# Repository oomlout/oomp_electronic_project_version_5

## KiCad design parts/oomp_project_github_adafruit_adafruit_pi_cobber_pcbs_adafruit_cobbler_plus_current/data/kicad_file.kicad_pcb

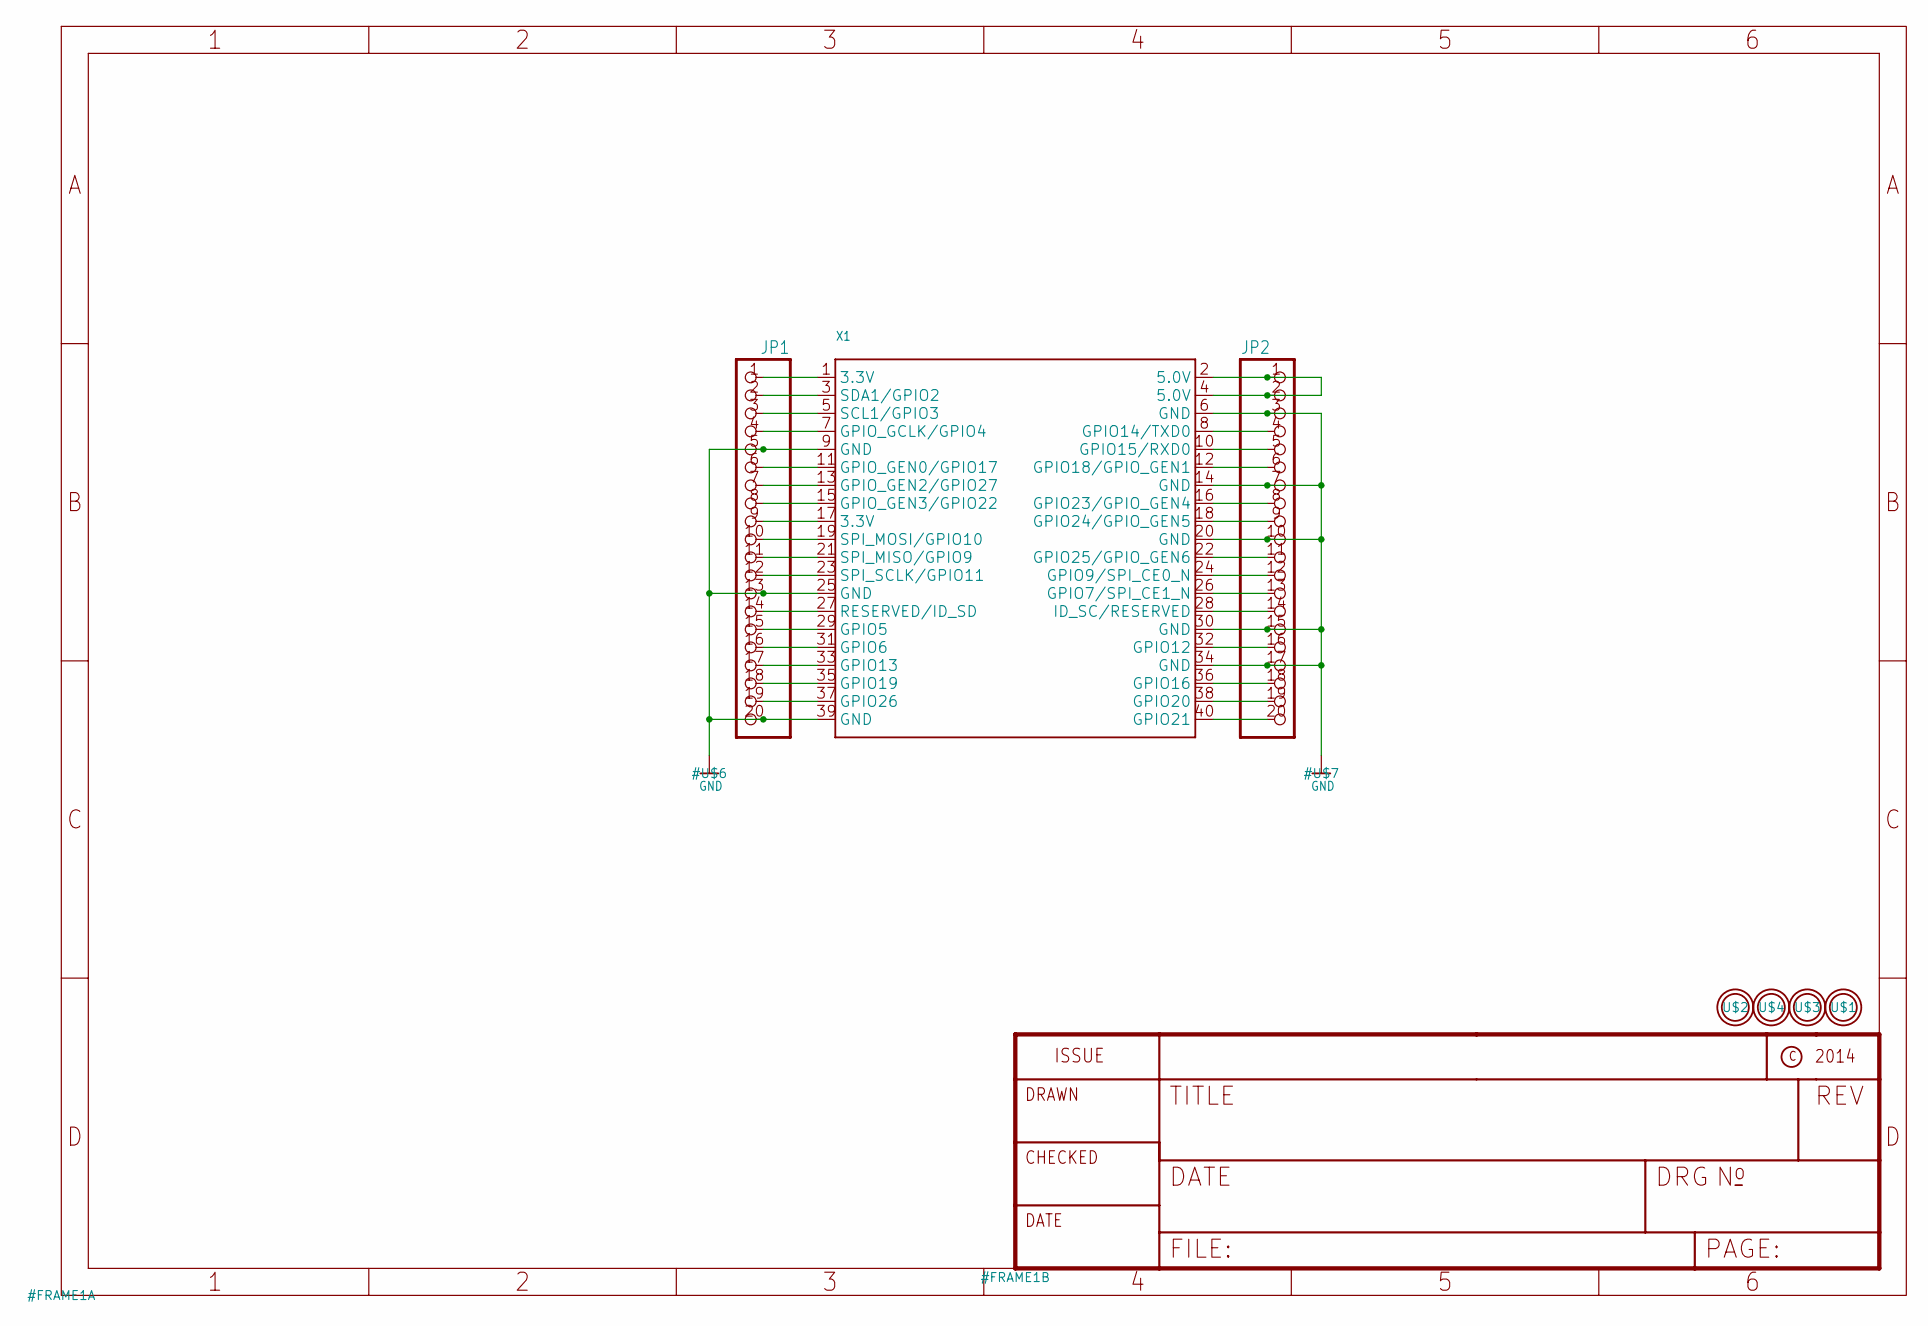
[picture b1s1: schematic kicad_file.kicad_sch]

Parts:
JP1, JP2: HEADER-1X20ROUND; 1X20_ROUND
U$1, U$2, U$3, U$4: MOUNTINGHOLE2.5_THICK; MOUNTINGHOLE_2.5_PLATED_THICK
X1: RASPBERRYPI_B+_IDC

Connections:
GND: JP1.5, JP1.13, JP1.20, JP2.3, JP2.7, JP2.10, JP2.15, JP2.17, X1.6 (GND), X1.9 (GND), X1.14 (GND), X1.20 (GND), X1.25 (GND), X1.30 (GND), X1.34 (GND), X1.39 (GND)
unnamed: JP2.1, JP2.2, X1.2 (5.0V), X1.4 (5.0V)
unnamed: JP2.4, X1.8 (GPIO14/TXD0)
unnamed: JP2.5, X1.10 (GPIO15/RXD0)
unnamed: JP2.6, X1.12 (GPIO18/GPIO_GEN1)
unnamed: JP2.8, X1.16 (GPIO23/GPIO_GEN4)
unnamed: JP2.9, X1.18 (GPIO24/GPIO_GEN5)
unnamed: JP2.11, X1.22 (GPIO25/GPIO_GEN6)
unnamed: JP2.12, X1.24 (GPIO9/SPI_CE0_N)
unnamed: JP2.13, X1.26 (GPIO7/SPI_CE1_N)
unnamed: JP2.14, X1.28 (ID_SC/RESERVED)
unnamed: JP2.16, X1.32 (GPIO12)
unnamed: JP2.18, X1.36 (GPIO16)
unnamed: JP2.19, X1.38 (GPIO20)
unnamed: JP2.20, X1.40 (GPIO21)
unnamed: JP1.1, X1.1 (3.3V)
unnamed: JP1.2, X1.3 (SDA1/GPIO2)
unnamed: JP1.3, X1.5 (SCL1/GPIO3)
unnamed: JP1.4, X1.7 (GPIO_GCLK/GPIO4)
unnamed: JP1.6, X1.11 (GPIO_GEN0/GPIO17)
unnamed: JP1.7, X1.13 (GPIO_GEN2/GPIO27)
unnamed: JP1.8, X1.15 (GPIO_GEN3/GPIO22)
unnamed: JP1.9, X1.17 (3.3V)
unnamed: JP1.10, X1.19 (SPI_MOSI/GPIO10)
unnamed: JP1.11, X1.21 (SPI_MISO/GPIO9)
unnamed: JP1.12, X1.23 (SPI_SCLK/GPIO11)
unnamed: JP1.14, X1.27 (RESERVED/ID_SD)
unnamed: JP1.15, X1.29 (GPIO5)
unnamed: JP1.16, X1.31 (GPIO6)
unnamed: JP1.17, X1.33 (GPIO13)
unnamed: JP1.18, X1.35 (GPIO19)
unnamed: JP1.19, X1.37 (GPIO26)

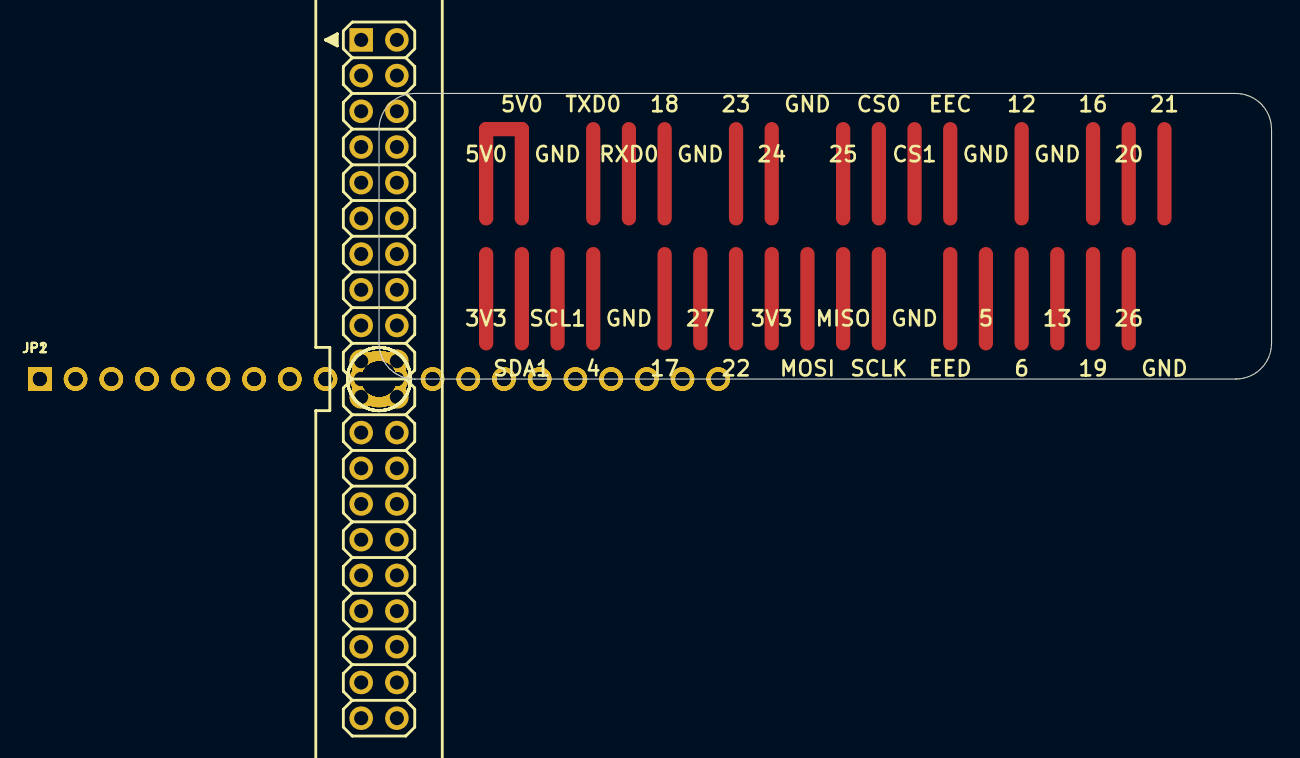
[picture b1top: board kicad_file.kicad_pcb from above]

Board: 2 copper layers, 63.5 x 20.3 mm, 7 parts (0 on the bottom side), 32 nets.

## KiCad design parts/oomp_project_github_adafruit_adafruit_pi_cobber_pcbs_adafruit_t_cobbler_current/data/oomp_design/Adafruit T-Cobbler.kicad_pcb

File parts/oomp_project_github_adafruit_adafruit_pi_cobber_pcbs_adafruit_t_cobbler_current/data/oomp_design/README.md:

# OOMP KiCad design copy

Open `Adafruit T-Cobbler.kicad_pro` (or the `.kicad_pcb` / `.kicad_sch`) in KiCad. Local OOMP libraries are under `libraries/`. Original inputs are preserved in [../original/](../original/).

Only verified unchanged installed KiCad defaults were renamed. Modified, custom, unmatched and unavailable items remain unchanged. Soldering variants are never swapped during conversion. Existing pad coordinates, nets and UUIDs are preserved.

See [conversion_report.yaml](conversion_report.yaml) for every conversion and skip. Copy this directory before editing; regeneration refuses to overwrite edited design files.

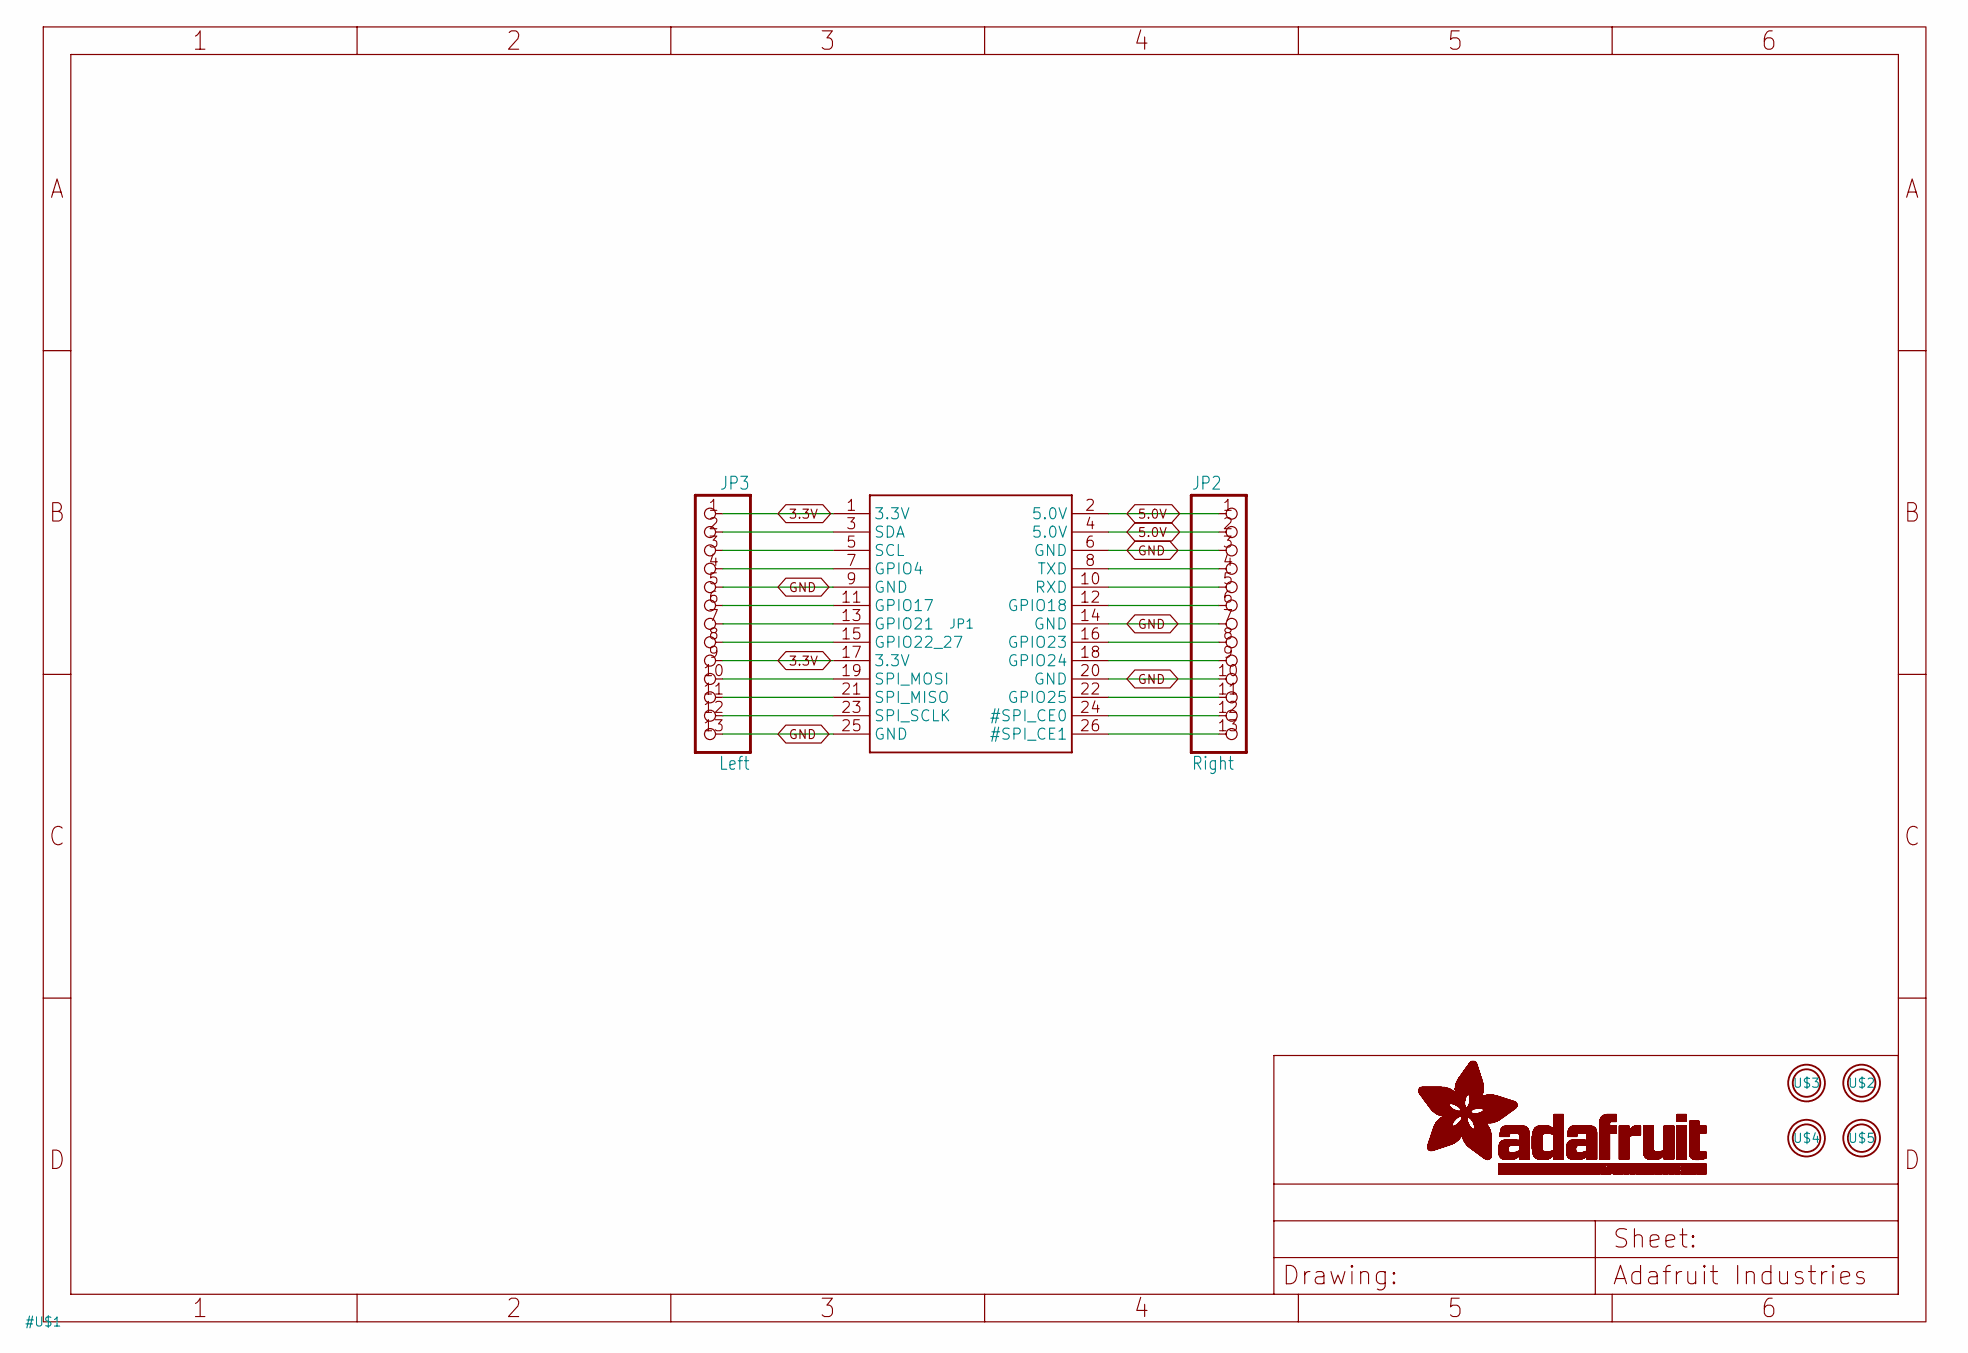
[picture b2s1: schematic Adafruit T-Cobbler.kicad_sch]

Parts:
JP1: PI; RASBERRYPI_IDC
JP2: Right; 1X13_ROUND_70
JP3: Left; 1X13_ROUND_70
U$2, U$3, U$4, U$5: MOUNTINGHOLE2.5; MOUNTINGHOLE_2.5_PLATED

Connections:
3.3V: JP1.1 (3.3V), JP1.17 (3.3V), JP3.1, JP3.9
5.0V: JP1.2 (5.0V), JP1.4 (5.0V), JP2.1, JP2.2
GND: JP1.6 (GND), JP1.9 (GND), JP1.14 (GND), JP1.20 (GND), JP1.25 (GND), JP2.3, JP2.7, JP2.10, JP3.5, JP3.13
unnamed: JP1.3 (SDA), JP3.2
unnamed: JP1.5 (SCL), JP3.3
unnamed: JP1.7 (GPIO4), JP3.4
unnamed: JP1.11 (GPIO17), JP3.6
unnamed: JP1.13 (GPIO21), JP3.7
unnamed: JP1.15 (GPIO22_27), JP3.8
unnamed: JP1.19 (SPI_MOSI), JP3.10
unnamed: JP1.21 (SPI_MISO), JP3.11
unnamed: JP1.23 (SPI_SCLK), JP3.12
unnamed: JP1.8 (TXD), JP2.4
unnamed: JP1.10 (RXD), JP2.5
unnamed: JP1.12 (GPIO18), JP2.6
unnamed: JP1.16 (GPIO23), JP2.8
unnamed: JP1.18 (GPIO24), JP2.9
unnamed: JP1.22 (GPIO25), JP2.11
unnamed: JP1.24 (#SPI_CE0), JP2.12
unnamed: JP1.26 (#SPI_CE1), JP2.13

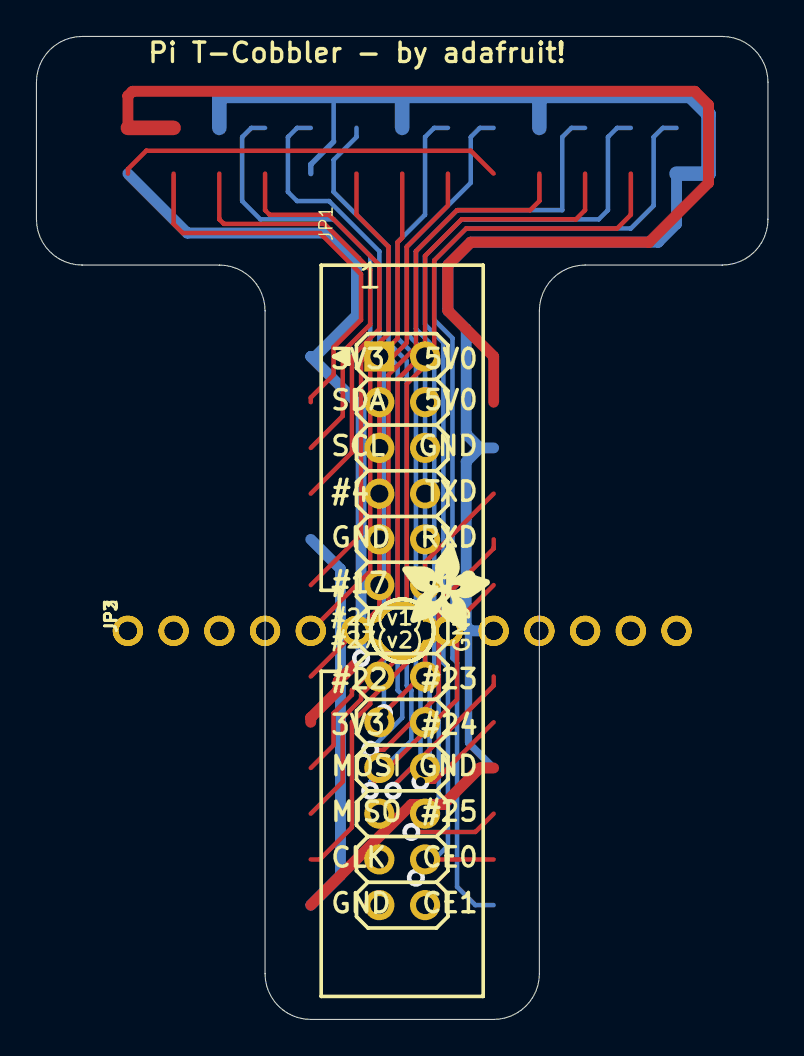
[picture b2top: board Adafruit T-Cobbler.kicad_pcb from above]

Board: 2 copper layers, 40.6 x 54.6 mm, 8 parts (0 on the bottom side), 20 nets.

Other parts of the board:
U$7: ADAFRUIT_5MM

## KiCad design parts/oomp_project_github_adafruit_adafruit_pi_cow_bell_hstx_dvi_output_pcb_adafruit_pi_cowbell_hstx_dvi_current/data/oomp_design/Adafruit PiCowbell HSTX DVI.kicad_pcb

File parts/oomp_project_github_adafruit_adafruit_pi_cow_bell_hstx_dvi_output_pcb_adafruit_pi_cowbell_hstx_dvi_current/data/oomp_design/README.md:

# OOMP KiCad design copy

Open `Adafruit PiCowbell HSTX DVI.kicad_pro` (or the `.kicad_pcb` / `.kicad_sch`) in KiCad. Local OOMP libraries are under `libraries/`. Original inputs are preserved in [../original/](../original/).

Only verified unchanged installed KiCad defaults were renamed. Modified, custom, unmatched and unavailable items remain unchanged. Soldering variants are never swapped during conversion. Existing pad coordinates, nets and UUIDs are preserved.

See [conversion_report.yaml](conversion_report.yaml) for every conversion and skip. Copy this directory before editing; regeneration refuses to overwrite edited design files.

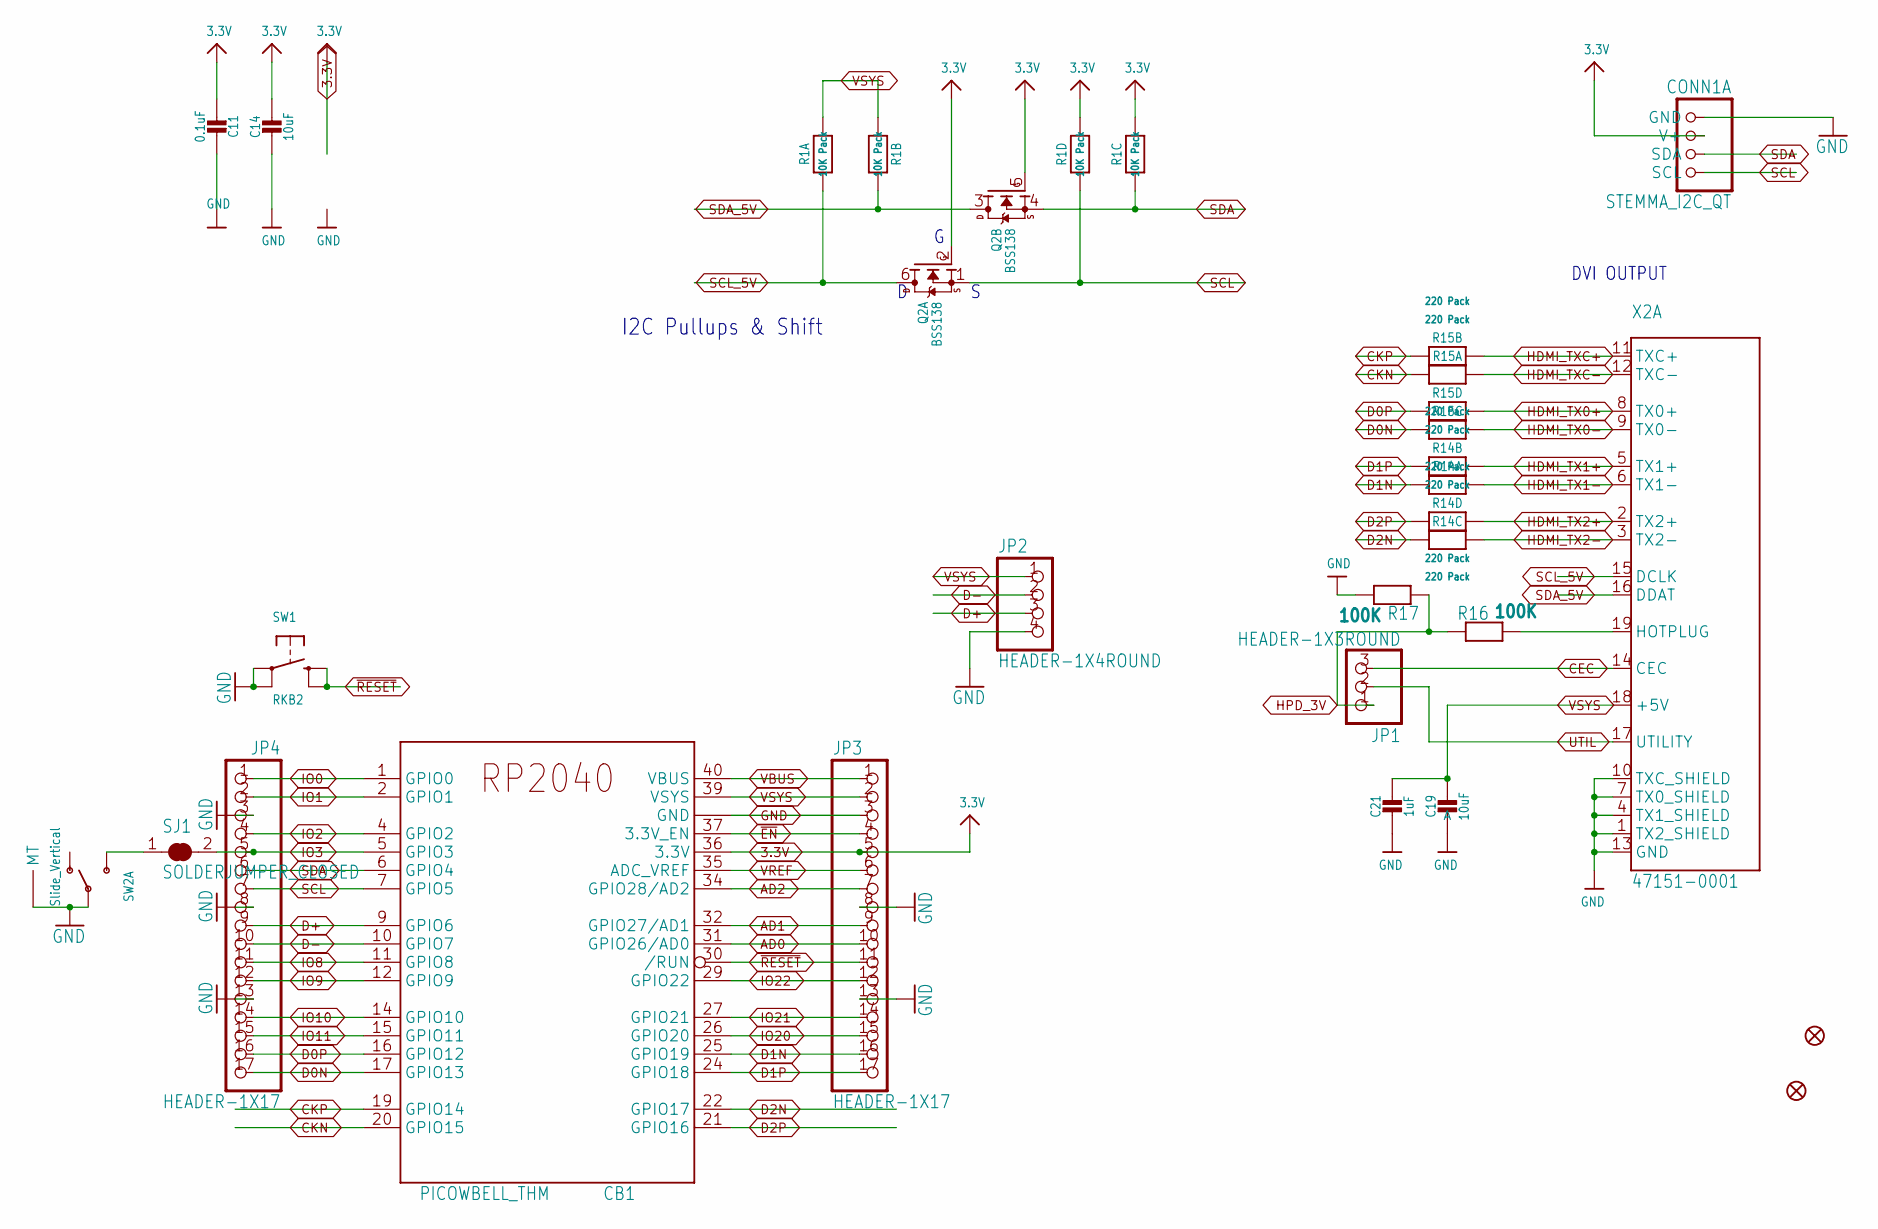
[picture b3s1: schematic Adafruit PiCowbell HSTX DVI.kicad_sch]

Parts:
C11: 0.1uF; 0603-NO
C14, C19: 10uF; 0805-NO
C21: 1uF; 0603-NO
CB1: PICOWBELL_THM
CONN1: STEMMA_I2C_QT; JST_SH4; LCSC C2845363
FID1, FID2: FIDUCIAL_1MM
JP1: HEADER-1X3ROUND; 1X03_ROUND
JP2: HEADER-1X4ROUND; 1X04_ROUND
JP3, JP4: HEADER-1X17; 1X17_ROUND70
Q2: BSS138; SOT363; JLC_ROTATION 270
R1: 10K Pack; RESPACK_4X0603
R14, R15: 220 Pack; RESPACK_4X0603
R16, R17: 100K; 0603-NO
SJ1: SOLDERJUMPER_CLOSED; SOLDERJUMPER_CLOSEDWIRE
SW1: RKB2; BTN_RKB2_4.6X2.8
SW2: Slide_Vertical; SPDT_SMT_SSSS811101
X2: 47151-0001; MINIHDMI_CNCTECH

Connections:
3.3V: C11.2, C14.1, CB1.36 (3.3V), CONN1.2 (V+), JP3.5, Q2.2 (G), Q2.5 (G), R1.5 (2), R1.6 (2)
AD0: CB1.31 (GPIO26/AD0), JP3.10
AD1: CB1.32 (GPIO27/AD1), JP3.9
AD2: CB1.34 (GPIO28/AD2), JP3.7
CEC: JP1.3, X2.14 (CEC)
CKN: CB1.20 (GPIO15), R15.8 (2)
CKP: CB1.19 (GPIO14), R15.7 (2)
D0N: CB1.17 (GPIO13), JP4.17, R15.6 (2)
D0P: CB1.16 (GPIO12), JP4.16, R15.5 (2)
D1N: CB1.25 (GPIO19), JP3.16, R14.8 (2)
D1P: CB1.24 (GPIO18), JP3.17, R14.7 (2)
D2N: CB1.22 (GPIO17), R14.6 (2)
D2P: CB1.21 (GPIO16), R14.5 (2)
D+: CB1.9 (GPIO6), JP2.3, JP4.9
D-: CB1.10 (GPIO7), JP2.2, JP4.10
GND: C11.1, C14.2, C19.2, C21.2, CB1.3 (GND), CB1.8 (GND), CB1.13 (GND), CB1.18 (GND), CB1.23 (GND), CB1.28 (GND), CB1.33 (GND), CB1.38 (GND), CONN1.1 (GND), JP2.4, JP3.3, JP3.8, JP3.13, JP4.3, JP4.8, JP4.13, R17.2, SW1.A, SW1.A' (P1), SW2.B, SW2.SUP1 (MT), SW2.SUP2 (MT), SW2.SUP3 (MT), SW2.SUP4 (MT), X2.1 (TX2_SHIELD), X2.4 (TX1_SHIELD), X2.7 (TX0_SHIELD), X2.10 (TXC_SHIELD), X2.13 (GND), X2.MNT1 (GND), X2.MNT2 (GND), X2.MNT3 (GND), X2.MNT4 (GND)
HDMI_TX0+: R15.4 (1), X2.8 (TX0+)
HDMI_TX0-: R15.3 (1), X2.9 (TX0-)
HDMI_TX1+: R14.2 (1), X2.5 (TX1+)
HDMI_TX1-: R14.1, X2.6 (TX1-)
HDMI_TX2+: R14.4 (1), X2.2 (TX2+)
HDMI_TX2-: R14.3 (1), X2.3 (TX2-)
HDMI_TXC+: R15.2 (1), X2.11 (TXC+)
HDMI_TXC-: R15.1, X2.12 (TXC-)
HPD: R16.2, X2.19 (HOTPLUG)
HPD_3V: JP1.1, R16.1, R17.1
IO0: CB1.1 (GPIO0), JP4.1
IO1: CB1.2 (GPIO1), JP4.2
IO2: CB1.4 (GPIO2), JP4.4
IO3: CB1.5 (GPIO3), JP4.5, SJ1.2
IO8: CB1.11 (GPIO8), JP4.11
IO9: CB1.12 (GPIO9), JP4.12
IO10: CB1.14 (GPIO10), JP4.14
IO11: CB1.15 (GPIO11), JP4.15
IO20: CB1.26 (GPIO20), JP3.15
IO21: CB1.27 (GPIO21), JP3.14
IO22: CB1.29 (GPIO22), JP3.12
unnamed: SJ1.1, SW2.C (S)
SCL: CB1.7 (GPIO5), CONN1.4 (SCL), JP4.7, Q2.1 (S), R1.4 (1)
SCL_5V: Q2.6 (D), R1.8 (2), X2.15 (DCLK)
SDA: CB1.6 (GPIO4), CONN1.3 (SDA), JP4.6, Q2.4 (S), R1.3 (1)
SDA_5V: Q2.3 (D), R1.7 (2), X2.16 (DDAT)
UTIL: JP1.2, X2.17 (UTILITY)
VBUS: CB1.40 (VBUS), JP3.1
VREF: CB1.35 (ADC_VREF), JP3.6
VSYS: C19.1, C21.1, CB1.39 (VSYS), JP2.1, JP3.2, R1.1, R1.2 (1), X2.18 (+5V)
~EN: CB1.37 (3.3V_EN), JP3.4
~RESET: CB1.30 (/RUN), JP3.11, SW1.B (S), SW1.B' (S1)

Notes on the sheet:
DVI OUTPUT
I2C Pullups & Shift

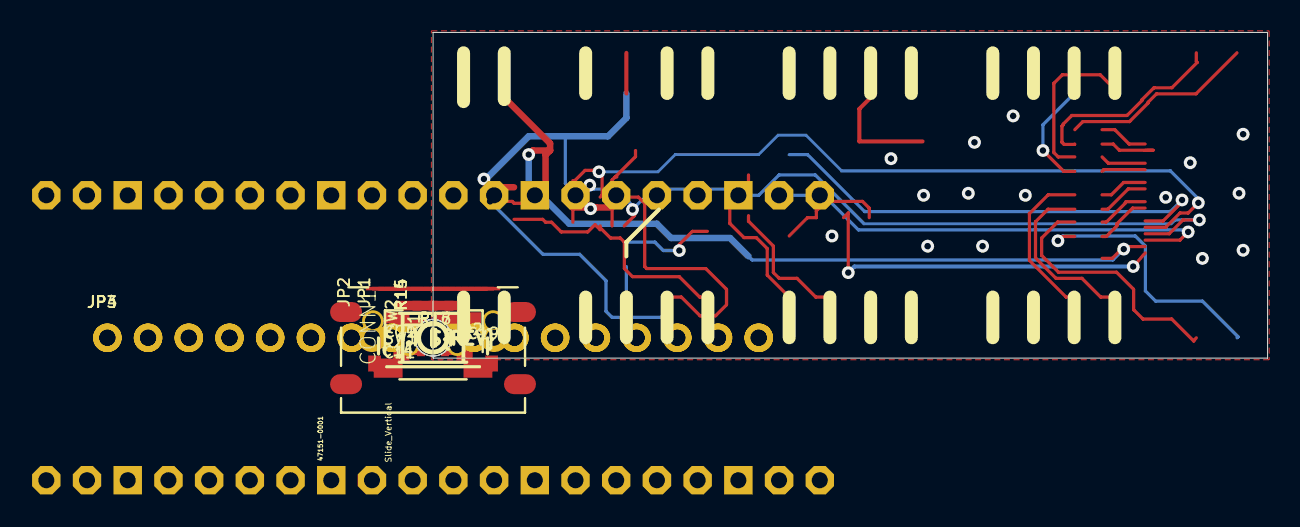
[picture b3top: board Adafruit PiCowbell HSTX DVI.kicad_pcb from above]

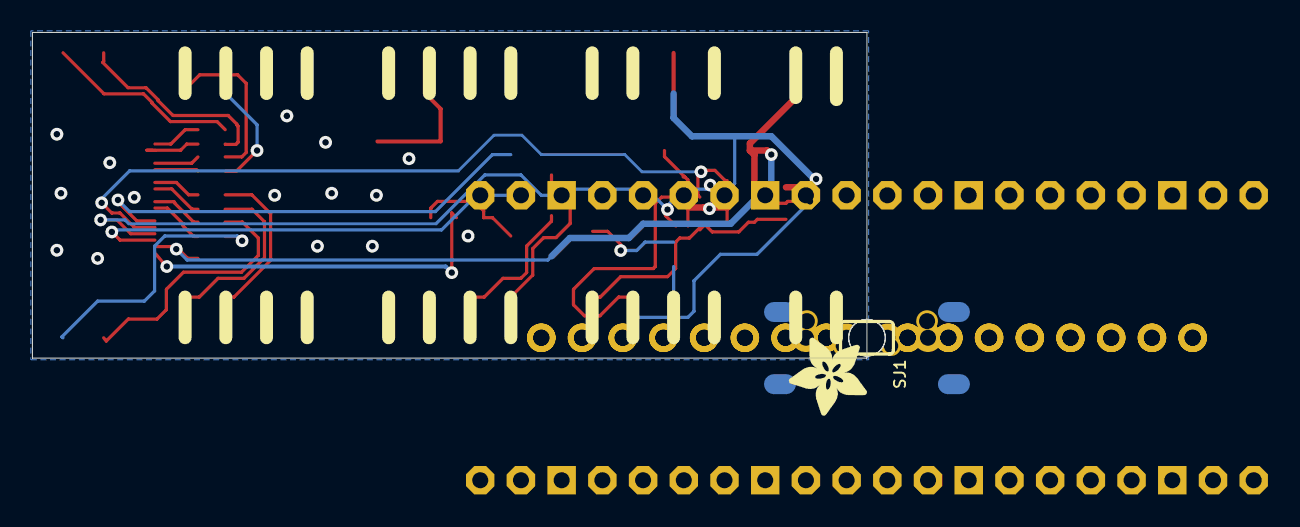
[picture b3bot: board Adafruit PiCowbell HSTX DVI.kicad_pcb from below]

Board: 2 copper layers, 52.1 x 20.3 mm, 110 parts (44 on the bottom side), 48 nets.

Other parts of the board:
PLABEL109: PLABEL109
PLABEL110: PLABEL110
PLABEL111: PLABEL111
PLABEL112: PLABEL112
PLABEL113: PLABEL113
PLABEL114: PLABEL114
PLABEL115: PLABEL115
PLABEL116: PLABEL116
PLABEL117: PLABEL117
PLABEL118: PLABEL118
PLABEL119: PLABEL119
PLABEL120: PLABEL120
PLABEL121: PLABEL121
PLABEL122: PLABEL122
PLABEL123: PLABEL123
PLABEL124: PLABEL124
PLABEL125: PLABEL125
PLABEL126: PLABEL126
PLABEL127: PLABEL127
PLABEL128: PLABEL128
PLABEL129: PLABEL129
PLABEL130: PLABEL130
PLABEL131: PLABEL131
PLABEL132: PLABEL132
PLABEL133: PLABEL133
PLABEL134: PLABEL134
PLABEL135: PLABEL135
PLABEL136: PLABEL136
PLABEL137: PLABEL137
PLABEL138: PLABEL138
PLABEL139: PLABEL139
PLABEL140: PLABEL140
PLABEL141: PLABEL141
PLABEL142: PLABEL142
PLABEL143: PLABEL143
PLABEL144: PLABEL144
PLABEL145: PLABEL145
PLABEL146: PLABEL146
PLABEL147: PLABEL147
PLABEL148: PLABEL148
PLABEL149: PLABEL149
PLABEL150: PLABEL150
PLABEL151: PLABEL151
PLABEL152: PLABEL152
PLABEL154: PLABEL154
PLABEL155: PLABEL155
PLABEL156: PLABEL156
PLABEL157: PLABEL157
PLABEL158: PLABEL158
PLABEL159: PLABEL159
PLABEL160: PLABEL160
PLABEL161: PLABEL161
PLABEL162: PLABEL162
PLABEL163: PLABEL163
PLABEL164: PLABEL164
PLABEL165: PLABEL165
PLABEL166: PLABEL166
PLABEL167: PLABEL167
PLABEL168: PLABEL168
PLABEL169: PLABEL169
PLABEL170: PLABEL170
PLABEL171: PLABEL171
PLABEL172: PLABEL172
PLABEL173: PLABEL173
PLABEL174: PLABEL174
PLABEL175: PLABEL175
PLABEL176: PLABEL176
PLABEL177: PLABEL177
PLABEL178: PLABEL178
PLABEL179: PLABEL179
PLABEL180: PLABEL180
PLABEL181: PLABEL181
PLABEL182: PLABEL182
PLABEL183: PLABEL183
PLABEL184: PLABEL184
PLABEL185: PLABEL185
PLABEL186: PLABEL186
PLABEL187: PLABEL187
PLABEL188: PLABEL188
PLABEL189: PLABEL189
PLABEL190: PLABEL190
PLABEL191: PLABEL191
PLABEL192: PLABEL192
PLABEL193: PLABEL193
U$1: ADAFRUIT_5MM
U$10: PCBFEAT-REV-040
UNK_HOLE_0: dummyfp0
UNK_HOLE_1: dummyfp1

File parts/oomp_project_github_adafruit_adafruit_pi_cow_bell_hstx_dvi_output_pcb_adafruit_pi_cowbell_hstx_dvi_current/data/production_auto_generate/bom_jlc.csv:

Comment,Designator,Footprint,LCSC Part #
,JP1,Adafruit PiCowbell HSTX DVI-import-fps:1X03_ROUND,C49257
,JP2,Adafruit PiCowbell HSTX DVI-import-fps:1X04_ROUND,C42431795
,"JP3,JP4",Adafruit PiCowbell HSTX DVI-import-fps:1X17_ROUND70,C49423291
,U$1,Adafruit PiCowbell HSTX DVI-import-fps:ADAFRUIT_5MM,
,U$10,Adafruit PiCowbell HSTX DVI-import-fps:PCBFEAT-REV-040,
,PLABEL109,Adafruit PiCowbell HSTX DVI-import-fps:PLABEL109,
,PLABEL110,Adafruit PiCowbell HSTX DVI-import-fps:PLABEL110,
,PLABEL111,Adafruit PiCowbell HSTX DVI-import-fps:PLABEL111,
,PLABEL112,Adafruit PiCowbell HSTX DVI-import-fps:PLABEL112,
,PLABEL113,Adafruit PiCowbell HSTX DVI-import-fps:PLABEL113,
,PLABEL114,Adafruit PiCowbell HSTX DVI-import-fps:PLABEL114,
,PLABEL115,Adafruit PiCowbell HSTX DVI-import-fps:PLABEL115,
,PLABEL116,Adafruit PiCowbell HSTX DVI-import-fps:PLABEL116,
,PLABEL117,Adafruit PiCowbell HSTX DVI-import-fps:PLABEL117,
,PLABEL118,Adafruit PiCowbell HSTX DVI-import-fps:PLABEL118,
,PLABEL119,Adafruit PiCowbell HSTX DVI-import-fps:PLABEL119,
,PLABEL120,Adafruit PiCowbell HSTX DVI-import-fps:PLABEL120,
,PLABEL121,Adafruit PiCowbell HSTX DVI-import-fps:PLABEL121,
,PLABEL122,Adafruit PiCowbell HSTX DVI-import-fps:PLABEL122,
,PLABEL123,Adafruit PiCowbell HSTX DVI-import-fps:PLABEL123,
,PLABEL124,Adafruit PiCowbell HSTX DVI-import-fps:PLABEL124,
,PLABEL125,Adafruit PiCowbell HSTX DVI-import-fps:PLABEL125,
,PLABEL126,Adafruit PiCowbell HSTX DVI-import-fps:PLABEL126,
,PLABEL127,Adafruit PiCowbell HSTX DVI-import-fps:PLABEL127,
,PLABEL128,Adafruit PiCowbell HSTX DVI-import-fps:PLABEL128,
,PLABEL129,Adafruit PiCowbell HSTX DVI-import-fps:PLABEL129,
,PLABEL130,Adafruit PiCowbell HSTX DVI-import-fps:PLABEL130,
,PLABEL131,Adafruit PiCowbell HSTX DVI-import-fps:PLABEL131,
,PLABEL132,Adafruit PiCowbell HSTX DVI-import-fps:PLABEL132,
,PLABEL133,Adafruit PiCowbell HSTX DVI-import-fps:PLABEL133,
,PLABEL134,Adafruit PiCowbell HSTX DVI-import-fps:PLABEL134,
,PLABEL135,Adafruit PiCowbell HSTX DVI-import-fps:PLABEL135,
,PLABEL136,Adafruit PiCowbell HSTX DVI-import-fps:PLABEL136,
,PLABEL137,Adafruit PiCowbell HSTX DVI-import-fps:PLABEL137,
,PLABEL138,Adafruit PiCowbell HSTX DVI-import-fps:PLABEL138,
,PLABEL139,Adafruit PiCowbell HSTX DVI-import-fps:PLABEL139,
,PLABEL140,Adafruit PiCowbell HSTX DVI-import-fps:PLABEL140,
,PLABEL141,Adafruit PiCowbell HSTX DVI-import-fps:PLABEL141,
,PLABEL142,Adafruit PiCowbell HSTX DVI-import-fps:PLABEL142,
,PLABEL143,Adafruit PiCowbell HSTX DVI-import-fps:PLABEL143,
,PLABEL144,Adafruit PiCowbell HSTX DVI-import-fps:PLABEL144,
,PLABEL145,Adafruit PiCowbell HSTX DVI-import-fps:PLABEL145,
,PLABEL146,Adafruit PiCowbell HSTX DVI-import-fps:PLABEL146,
,PLABEL147,Adafruit PiCowbell HSTX DVI-import-fps:PLABEL147,
,PLABEL148,Adafruit PiCowbell HSTX DVI-import-fps:PLABEL148,
,PLABEL149,Adafruit PiCowbell HSTX DVI-import-fps:PLABEL149,
,PLABEL150,Adafruit PiCowbell HSTX DVI-import-fps:PLABEL150,
,PLABEL151,Adafruit PiCowbell HSTX DVI-import-fps:PLABEL151,
,PLABEL152,Adafruit PiCowbell HSTX DVI-import-fps:PLABEL152,
,PLABEL154,Adafruit PiCowbell HSTX DVI-import-fps:PLABEL154,
,PLABEL155,Adafruit PiCowbell HSTX DVI-import-fps:PLABEL155,
,PLABEL156,Adafruit PiCowbell HSTX DVI-import-fps:PLABEL156,
,PLABEL157,Adafruit PiCowbell HSTX DVI-import-fps:PLABEL157,
,PLABEL158,Adafruit PiCowbell HSTX DVI-import-fps:PLABEL158,
,PLABEL159,Adafruit PiCowbell HSTX DVI-import-fps:PLABEL159,
,PLABEL160,Adafruit PiCowbell HSTX DVI-import-fps:PLABEL160,
,PLABEL161,Adafruit PiCowbell HSTX DVI-import-fps:PLABEL161,
,PLABEL162,Adafruit PiCowbell HSTX DVI-import-fps:PLABEL162,
,PLABEL163,Adafruit PiCowbell HSTX DVI-import-fps:PLABEL163,
,PLABEL164,Adafruit PiCowbell HSTX DVI-import-fps:PLABEL164,
,PLABEL165,Adafruit PiCowbell HSTX DVI-import-fps:PLABEL165,
,PLABEL166,Adafruit PiCowbell HSTX DVI-import-fps:PLABEL166,
,PLABEL167,Adafruit PiCowbell HSTX DVI-import-fps:PLABEL167,
,PLABEL168,Adafruit PiCowbell HSTX DVI-import-fps:PLABEL168,
,PLABEL169,Adafruit PiCowbell HSTX DVI-import-fps:PLABEL169,
,PLABEL170,Adafruit PiCowbell HSTX DVI-import-fps:PLABEL170,
,PLABEL171,Adafruit PiCowbell HSTX DVI-import-fps:PLABEL171,
,PLABEL172,Adafruit PiCowbell HSTX DVI-import-fps:PLABEL172,
,PLABEL173,Adafruit PiCowbell HSTX DVI-import-fps:PLABEL173,
,PLABEL174,Adafruit PiCowbell HSTX DVI-import-fps:PLABEL174,
,PLABEL175,Adafruit PiCowbell HSTX DVI-import-fps:PLABEL175,
,PLABEL176,Adafruit PiCowbell HSTX DVI-import-fps:PLABEL176,
,PLABEL177,Adafruit PiCowbell HSTX DVI-import-fps:PLABEL177,
,PLABEL178,Adafruit PiCowbell HSTX DVI-import-fps:PLABEL178,
,PLABEL179,Adafruit PiCowbell HSTX DVI-import-fps:PLABEL179,
,PLABEL180,Adafruit PiCowbell HSTX DVI-import-fps:PLABEL180,
,PLABEL181,Adafruit PiCowbell HSTX DVI-import-fps:PLABEL181,
,PLABEL182,Adafruit PiCowbell HSTX DVI-import-fps:PLABEL182,
,PLABEL183,Adafruit PiCowbell HSTX DVI-import-fps:PLABEL183,
,PLABEL184,Adafruit PiCowbell HSTX DVI-import-fps:PLABEL184,
,PLABEL185,Adafruit PiCowbell HSTX DVI-import-fps:PLABEL185,
,PLABEL186,Adafruit PiCowbell HSTX DVI-import-fps:PLABEL186,
,PLABEL187,Adafruit PiCowbell HSTX DVI-import-fps:PLABEL187,
,PLABEL188,Adafruit PiCowbell HSTX DVI-import-fps:PLABEL188,
,PLABEL189,Adafruit PiCowbell HSTX DVI-import-fps:PLABEL189,
,PLABEL190,Adafruit PiCowbell HSTX DVI-import-fps:PLABEL190,
,PLABEL191,Adafruit PiCowbell HSTX DVI-import-fps:PLABEL191,
,PLABEL192,Adafruit PiCowbell HSTX DVI-import-fps:PLABEL192,
,PLABEL193,Adafruit PiCowbell HSTX DVI-import-fps:PLABEL193,
0.1uF,C11,Adafruit PiCowbell HSTX DVI-import-fps:0603-NO,C14663
100K,"R16,R17",Adafruit PiCowbell HSTX DVI-import-fps:0603-NO,C25803
10K Pack,R1,Adafruit PiCowbell HSTX DVI-import-fps:RESPACK_4X0603,C98220
10uF,"C14,C19",Adafruit PiCowbell HSTX DVI-import-fps:0805-NO,
1uF,C21,Adafruit PiCowbell HSTX DVI-import-fps:0603-NO,C5673
220 Pack,"R14,R15",Adafruit PiCowbell HSTX DVI-import-fps:RESPACK_4X0603,
47151-0001,X2,Adafruit PiCowbell HSTX DVI-import-fps:MINIHDMI_CNCTECH,
BSS138,Q2,Adafruit PiCowbell HSTX DVI-import-fps:SOT363,
PICOWBELL_THM,CB1,Adafruit PiCowbell HSTX DVI-import-fps:PICOWBELL_THM,
RKB2,SW1,Adafruit PiCowbell HSTX DVI-import-fps:BTN_RKB2_4.6X2.8,
Slide_Vertical,SW2,Adafruit PiCowbell HSTX DVI-import-fps:SPDT_SMT_SSSS811101,
STEMMA_I2C_QT,CONN1,Adafruit PiCowbell HSTX DVI-import-fps:JST_SH4,C160404

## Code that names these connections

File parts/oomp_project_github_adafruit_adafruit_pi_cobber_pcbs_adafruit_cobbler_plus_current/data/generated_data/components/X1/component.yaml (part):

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        pin_number: '4'
        pin_name: 5.0V
    - number: '3'
      name: SDA1/GPIO2
      electrical_type: bidirectional
      graphic_style: line
      local_position:
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        pin_number: '2'
        pin_name: 5.0V
    - number: '5'
      name: SCL1/GPIO3
      electrical_type: bidirectional
      graphic_style: line
      local_position:
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        pin_number: '39'
        pin_name: GND
    - number: '7'
      name: GPIO_GCLK/GPIO4
      electrical_type: bidirectional
      graphic_style: line
      local_position:
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        pin_number: '4'
        pin_name: '4'
    - number: '8'
      name: GPIO14/TXD0
      electrical_type: bidirectional
      graphic_style: line
      local_position:
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        pin_number: '39'
        pin_name: GND
    - number: '10'
      name: GPIO15/RXD0
      electrical_type: bidirectional
      graphic_style: line
      local_position:
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        pin_number: '5'
        pin_name: '5'
    - number: '11'
      name: GPIO_GEN0/GPIO17
      electrical_type: bidirectional
      graphic_style: line
      local_position:
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        pin_number: '6'
        pin_name: '6'
    - number: '12'
      name: GPIO18/GPIO_GEN1
      electrical_type: bidirectional
      graphic_style: line
      local_position:
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        pin_number: '6'
        pin_name: '6'
    - number: '13'
      name: GPIO_GEN2/GPIO27
      electrical_type: bidirectional
      graphic_style: line
      local_position:
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        pin_number: '39'
        pin_name: GND
    - number: '15'
      name: GPIO_GEN3/GPIO22
      electrical_type: bidirectional
      graphic_style: line
      local_position:
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        pin_number: '8'
        pin_name: '8'
    - number: '16'
      name: GPIO23/GPIO_GEN4
      electrical_type: bidirectional
      graphic_style: line
      local_position:
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        pin_number: '9'
        pin_name: '9'
    - number: '18'
      name: GPIO24/GPIO_GEN5
      electrical_type: bidirectional
      graphic_style: line
      local_position:
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        pin_number: '9'
        pin_name: '9'
    - number: '19'
      name: SPI_MOSI/GPIO10
      electrical_type: bidirectional
      graphic_style: line
      local_position:
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        pin_number: '39'
        pin_name: GND
    - number: '21'
      name: SPI_MISO/GPIO9
      electrical_type: input
      graphic_style: line
      local_position:
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        pin_number: '11'
        pin_name: '11'
    - number: '22'
      name: GPIO25/GPIO_GEN6
      electrical_type: bidirectional
      graphic_style: line
      local_position:
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        pin_number: '11'
        pin_name: '11'
    - number: '23'
      name: SPI_SCLK/GPIO11
      electrical_type: bidirectional
      graphic_style: line
      local_position:
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        pin_number: '12'
        pin_name: '12'
    - number: '24'
      name: GPIO9/SPI_CE0_N
      electrical_type: bidirectional
      graphic_style: line
      local_position:
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        pin_number: '39'
        pin_name: GND
    - number: '26'
      name: GPIO7/SPI_CE1_N
      electrical_type: bidirectional
      graphic_style: line
      local_position:
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        pin_number: '14'
        pin_name: '14'
    - number: '29'
      name: GPIO5
      electrical_type: bidirectional
      graphic_style: line
      local_position:
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        pin_number: '39'
        pin_name: GND
    - number: '31'
      name: GPIO6
      electrical_type: bidirectional
      graphic_style: line
      local_position:
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        pin_number: '16'
        pin_name: '16'
    - number: '32'
      name: GPIO12
      electrical_type: bidirectional
      graphic_style: line
      local_position:
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        pin_number: '16'
        pin_name: '16'
    - number: '33'
      name: GPIO13
      electrical_type: bidirectional
      graphic_style: line
      local_position:
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        pin_number: '39'
        pin_name: GND
    - number: '35'
      name: GPIO19
      electrical_type: bidirectional
      graphic_style: line
      local_position:
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        pin_number: '18'
        pin_name: '18'
    - number: '36'
      name: GPIO16
      electrical_type: bidirectional
      graphic_style: line
      local_position:
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        pin_number: '18'
        pin_name: '18'
    - number: '37'
      name: GPIO26
      electrical_type: bidirectional
      graphic_style: line
      local_position:
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        pin_number: '19'
        pin_name: '19'
    - number: '38'
      name: GPIO20
      electrical_type: bidirectional
      graphic_style: line
      local_position:
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        pin_number: '34'
        pin_name: GND
    - number: '40'
      name: GPIO21
      electrical_type: bidirectional
      graphic_style: line
      local_position:
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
